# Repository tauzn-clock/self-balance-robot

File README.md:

## Self Balance Robot

This repo serves as a record of my attempt to build a self-balancing robot (affectionately called rat :D ).

https://github.com/tauzn-clock/self-balancing-robot/assets/72295649/7475527e-0695-4e05-951b-1d8318b3db41

### Bill of Materials:
- [Node MCU](https://www.ebay.co.uk/itm/263729724888)
- [MPU6050 IMU](https://www.amazon.co.uk/dp/B0957SJL6D?psc=1&ref=ppx_yo2ov_dt_b_product_details)
- [L298N H-Bridge Controller + Motors](https://www.amazon.co.uk/dp/B07ZT5CCFV?psc=1&ref=ppx_yo2ov_dt_b_product_details)
- 9V Battery
- Ribbon Cables
- Custom PCB Board (See `PCB_files`)

### Installation
> [!WARNING]  
> Turn off 9V power when connected to Node MCU
1) Download Visual Studio Code
2) Install the [Platform IO Extension](https://platformio.org/)
3) Build `/src/main.cpp` and flash to Node MCU

### Tips on Tuning
- Tuning Parameters found under `/include/control/balance.cpp` are specific to my robot. These may defer if different components are used.
- Typically, the IMU comes with a slight offset specific to each component.

### Future Improvements:
- Mounting holes in PCB board are too small for M3 threads, and require some filing
- Shift wheel motor mounting points closer to the edge
- After prolonged usage, wheels do not rotate at magnitudes lower than 0.5 (Due to friction within the motor?)
- Include directional control based on Node MCU's Wifi Module?

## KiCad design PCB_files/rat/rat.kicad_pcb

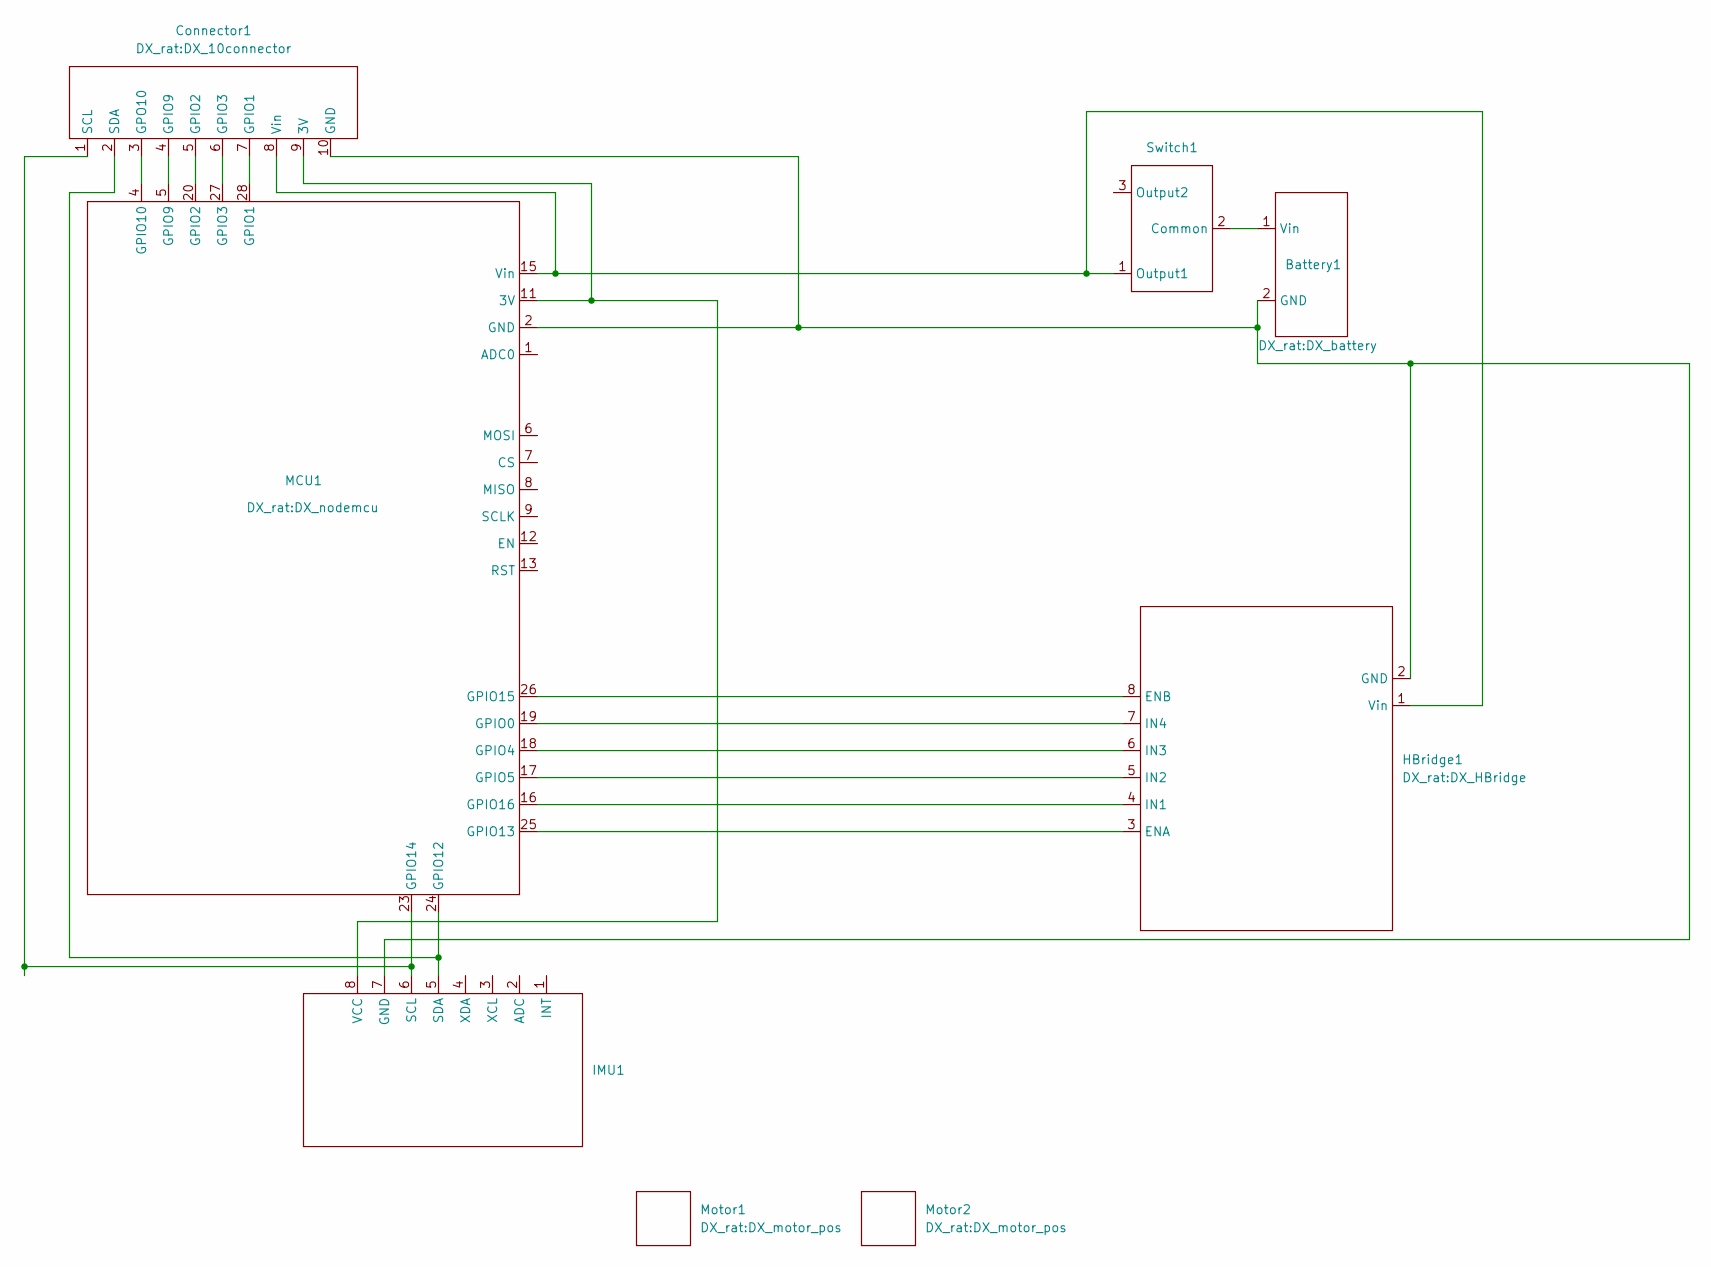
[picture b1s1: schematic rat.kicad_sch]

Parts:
Battery1: DX_battery
Connector1: DX_10connector
HBridge1: DX_HBridge
IMU1: DX_imu
MCU1: DX_nodemcu
Motor1, Motor2: DX_motor_pos
Switch1: DX_Switch

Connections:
unnamed: Battery1.2 (GND), Connector1.10 (GND), HBridge1.2 (GND), IMU1.7 (GND), MCU1.2 (GND), MCU1.10 (GND), MCU1.14 (GND), MCU1.22 (GND), MCU1.29 (GND)
unnamed: Battery1.1 (Vin), Switch1.2 (Common)
unnamed: Connector1.9 (3V), IMU1.8 (VCC), MCU1.11 (3V), MCU1.21 (3V), MCU1.30 (3V)
unnamed: Connector1.7 (GPIO1), MCU1.28 (GPIO1)
unnamed: Connector1.5 (GPIO2), MCU1.20 (GPIO2)
unnamed: Connector1.6 (GPIO3), MCU1.27 (GPIO3)
unnamed: Connector1.4 (GPIO9), MCU1.5 (GPIO9)
unnamed: Connector1.3 (GPO10), MCU1.4 (GPIO10)
unnamed: Connector1.1 (SCL), IMU1.6 (SCL), MCU1.23 (GPIO14)
unnamed: Connector1.2 (SDA), IMU1.5 (SDA), MCU1.24 (GPIO12)
unnamed: Connector1.8 (Vin), HBridge1.1 (Vin), MCU1.15 (Vin), Switch1.1 (Output1)
unnamed: HBridge1.3 (ENA), MCU1.25 (GPIO13)
unnamed: HBridge1.8 (ENB), MCU1.26 (GPIO15)
unnamed: HBridge1.4 (IN1), MCU1.16 (GPIO16)
unnamed: HBridge1.5 (IN2), MCU1.17 (GPIO5)
unnamed: HBridge1.6 (IN3), MCU1.18 (GPIO4)
unnamed: HBridge1.7 (IN4), MCU1.19 (GPIO0)

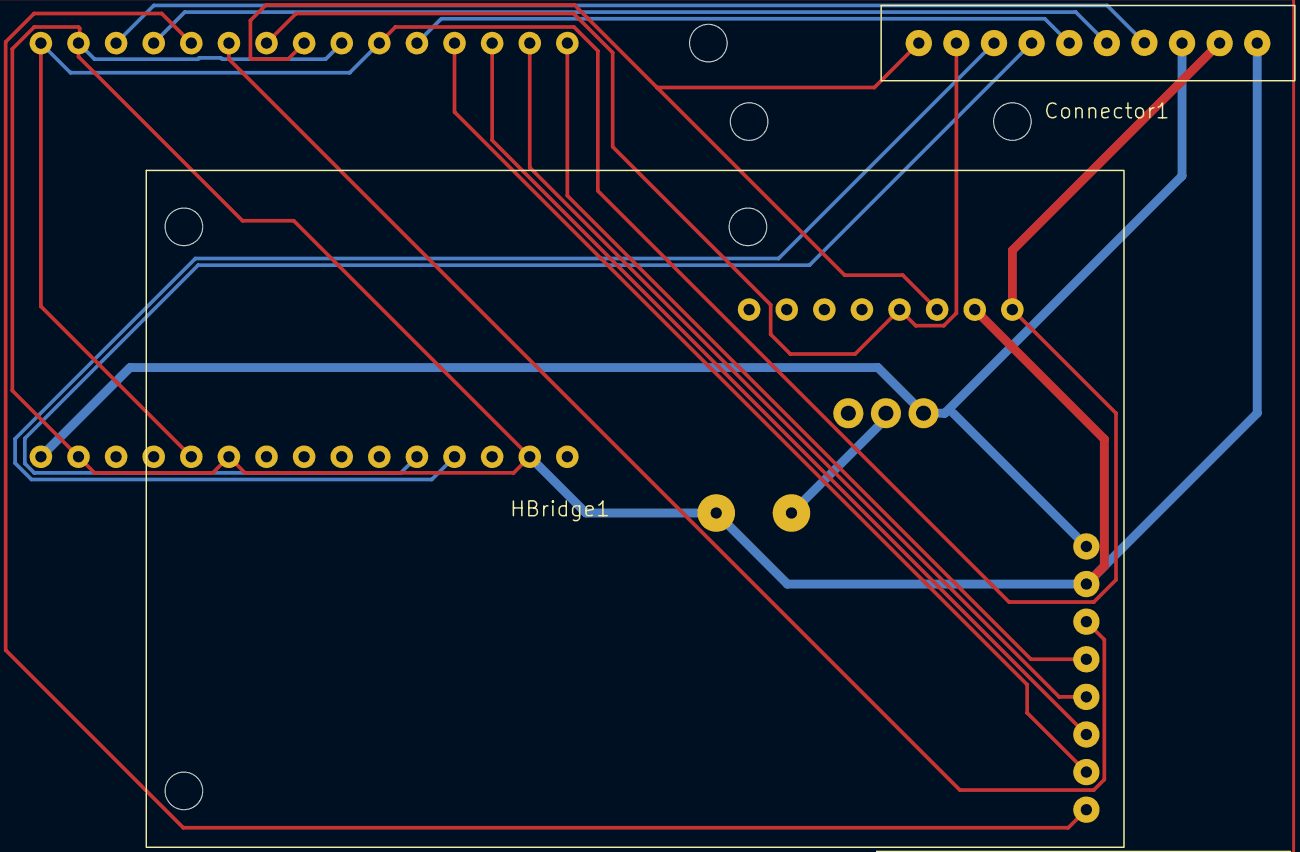
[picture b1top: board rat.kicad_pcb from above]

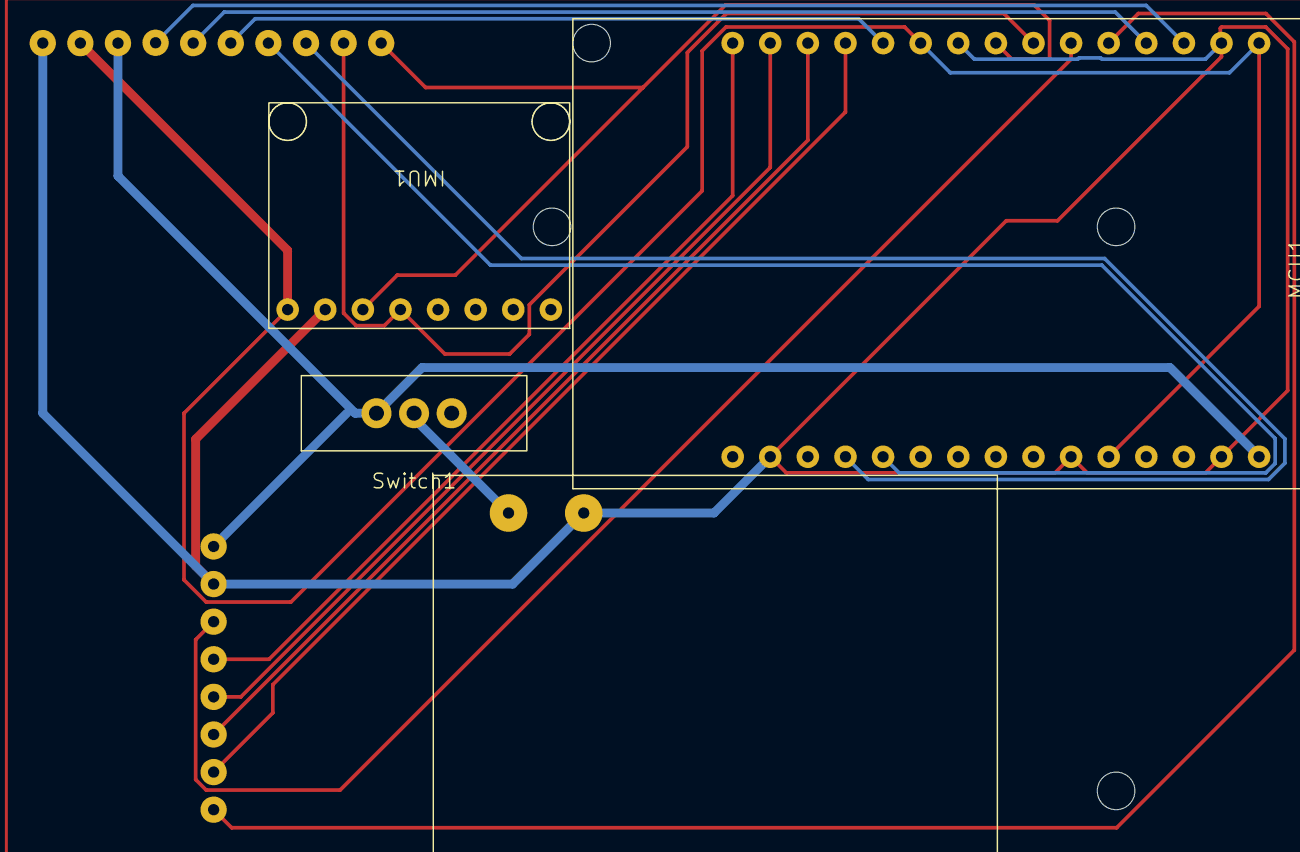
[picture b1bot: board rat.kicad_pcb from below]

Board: 2 copper layers, 8 parts (4 on the bottom side), 17 nets.

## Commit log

2023-07-29 first init
2023-07-29 add pcb files
2023-07-29 clean up
2023-07-30 basic wifi examples
2023-07-30 basic base station
2023-07-30 give up on oop for wifi
2023-07-30 remove all httpspages
2023-08-03 ugly control
2023-08-04 i give up
2023-09-18 removed unnecessary files
2023-09-18 remove .vscode
2023-09-18 demo video
